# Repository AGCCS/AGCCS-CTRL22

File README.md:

AGCCS-CTRL22
============

We propose a design for a network of EV charging stations compliant to the CCS standard. The repository is organised as follows:

- [./circuit](./circuit/): hardware platform, incl. schematics and a HowTo on firmware installation
- [./ctrl22c](./ctrl22c/): AVR firmware to control the charging process
- [./demesh](./demesh/): ESP32 firmware to organise messaging over a wireless mesh network
- [./monitor](./monitor/): server software for overall control and monitoring of the charging station network
- [./utils](./utils/): scripts to facilitate first-installation and debugging
- [./arduino](./arduino/): Arduino IDE compatible firmware for stand-alone operation (side track)
- [./doc](./doc/): Thesis and other documents regarding this project

**DISCLAIMER 1.** We do not provide a turn-key solution and do not plan to do so in near future. Rather we invite the enthusiast to actively contribute or to passively make use of our collection of resources and to share their experience. We started this project in 2019 and are making steady progress. However, there is still a relevant todo-list. 

**DISCLAIMER 2.** All material provided in this repository comes *'as is'* with no explicit or implied warranty. In particular, the installation of equipment that directly connects to mains power should only by considered by individuals with adequate skills and with particular care.

## Motivation

The Combined Charging System (CCS) provides a specification for low-cost home-charging of electric vehicles (EVs) with up to 22kW. It is based on a simplistic protocol by which the vehicle and the charging station negotiate available power. Of-the-shelf wall-boxes forward the common 3x230V supply at an adjustable current limit to the vehicle via the CCS standard.

The aim of this project is to scale the simplicity of the low-cost single-user wallbox approach to larger parking lots in order to address appartment buildings or shopping venues. These configurations are characterised by a limited and possibly varying amount of available power. Hence, a fixed allocation per parking slot would be inefficient. Instead, we seek for an environment by which individual charging spots communicate and negotiate the power distribution dynamically. Conveivable schemes include first-comes-first-serve, fairness-based-energy-distribution, or ready-to-go-by-schedule. Optionally, an external agent may limit the ussage of non-renewable enery in favour of e.g. available solar power at the given time to the day. 

Our implementation consists of three main components

- a **hardware platform** to implement a relevant subset of the CCS standard
-  **node firmware** to control the charging process and to establish a communication network
- a centralised host for dynamic power allocation and **monitoring** 

All three components are open source and can be hence adapted to best fit a variety of application scenarios.

*From the time we started this project, the market changed a lot and, as of 2021, a number wallboxes with similar features are readily available. However, we believe the an open source approach is still valuable.*

## Hardware Platform

[Our hardware platform](./circuit/) consists of 

+ relevant analog circuitry to implement the specified electronic characteristics
+ an AVR series uC to control the charging process, and
+ an ESP32 SoC to provide means of wireless communication. 

Regarding the analog circuitry, our implementation is derived from the [SmatEVSE project](https://github.com/SmartEVSE). Regarding the uC, we opted for an AVR ATmega to allow for conveniently programming within the Arduino IDE in a long term perspective --- although at this stage the firmware we provide comes 'bare bone' for performance reasons. Regarding the ESP32 SoC, we are fascinated by the powerful SDKs available from Espressif. For our hardware platform, we provide schematics and a PCB Layout, both in editable KiCad format. More detailed documentation is provided in [./circuit/README.md](./circuit/). 

## Node Firmware

Each charging spot comes with an AVR uC for time/safety critical low-level behaviour which communicates via RS232 with an ESP32 for inter-node networking. While the AVR is programed from scratch, the ESP32 firmware builds on the MDF-SDK for wireless mesh-networking. From the latter, we expect a comparatively large area of coverage without additional infrastructure such as Wifi repeaters. Our mesh network subscribes to and publishes from an MQTT broker and is thus interoperable with a wide range of available home automation software. Both, the AVR firmware and the ESP firmware support OTA updates, i.e., no crawling along the parking lot to plug in programming adaptors. More detailed documentation is given by in [./ctrl22c/README.md](./ctrl22c/) for the AVR firmware and by  [./demesh/README.md](./demesh/) for the ESP32 firmware.

## Monitoring Server

At the time of writing, we only provide an elementary monitoring server implemented in Python
for development/testing purposes; see [./utils/README.md](./utils/). This will be substantially updated in the
very near future --- stay tuned.

## Prototype

The below photo shows our hardware (rev 1.2) assembled in an enclosure to include mains contactors, residual current detector/protection and current transformers. It is supplied by three-phases at 32A via the CEE plug on the left, with power forwarded to the CCS 2 outlet on the right; see [Installation](./Installation.md) for details on the external components and the wiring. 

Test run on an individual vehicle (type Opel Corsa) varying from 3kW to 11kW ... lets control the power ;-)

## How/Where/Why to Get Started

Well, no turn-key solution ... but perhaps some interesting venues for the enthusiast:

- If you are interested in hardware and want to assemble your very own CCS implementation there are only a view likewise open projects, e.g., [SmartEVSE](https://www.smartevse.nl/) and [OpenEVSE](https://www.openevse.com/). You are invited to inspect our proposed [./circuit](./circuit/), compare the specifications and take your choice.
- If you are interested in ESP32 mesh networking, perhaps for a completely different target application, feel free to run our implementation [./demesh](./demesh/) in stand-alone mode on common ESP32 dev-boards or more conveniently on M5Sticks. Features include OTA firmware update, control via MQTT and/or plain TCP sockets, synchronised system time, Optiboot (STK500) programming of a target AVR uC.

## Contributors

This project is an initiative by Christoph Pflaum and Thomas Moor, both with FAU/Erlangen/Germany. We appreciate the following contributions by our students/staff.

- Roland Kießling: electrics/electronics lab support, including design and assembly of the prototype enclosures. 

- Pascal Thurnherr: [BA thesis](./doc/Bachelorarbeit_Pascal_Thurnherr.pdf) , _Aufbau und Test einer Ladeneinrichtung für Elektrofahrzeuge nach IEC62169_, FAU/Erlangen 2020; see also [this project](https://github.com/dreadnomad/FGCCS-Ctrl22).

- Antoine Schultz: BA thesis *Firmwareverwaltung drahtlos vernetzter Kleinstrechner mit angekoppelten Mikroprozessoren*, FAU/Erlangen 2020.

- Xinhuang Gong: [MA thesis](./doc/Masterthesis_Xinhuang_Gong.pdf), *Software Infrastructure for a Distributed EV Charging System*, FAU/Erlangen 2021.

- Mark Brieger: MA thesis, *IT Security in home automation — Analysis of connected EV charging stations*, FAU/Erlangen 2021. The study includes a detailed security analysis of the AGCCS hard- and software, and, doing so, reveals a number of relevant vulnerabilities. The majority of these issues has been fixed by Mark, the remainder will be addressed in due course.   

## Acknowledgements

The Wikipedia articles on the [SAE 1772](https://de.wikipedia.org/wiki/SAE_J1772nd), the [IEC 62196](https://de.wikipedia.org/wiki/IEC_62196)  and the [IEC 62196 Type 2](https://de.wikipedia.org/wiki/IEC_62196_Typ_2) standards provide an excellent entry point to learn about EV charging technology and we would like to thank the respective authors for their effort. Regarding the electrical engineeering aspects of this project, we hereby acknowledge the projects [SmartEVSE](https://www.smartevse.nl/) and [OpenEVSE](https://www.openevse.com/), which make their circuitry available for us to inspect and re-use. Starting from scratch would have been so much more tedious. On a more general scale, we appreciate the fact that nowerdays relevent software tools are made freely available, such as the [KiCad EDA](https://kicad.org) , the [Espressif SDKs](https://github.com/espressif), and the [GCC](https://gcc.gnu.org/)-based XTENSA and AVR toolchains, naming only the ones most crucial for our project.

## Copyright/License

All software compents in this project are _"Copyright by the Authors"_ and have been developed independently and from scratch. We provide them as _"Open Source"_ under terms of the MIT License, the Apache License, and/or the GPL, as indicated in the respective code headers. In particular, you are invited to re-cycle whatever you find useful in whatever project you are after. In the case you feel that you gained a relevant benefit from our work, we would appreciate an acknowledgement, e.g., by linking to our GitHub repository. Regarding the hardware circuitry, our work in relevant aspects is a derivative of [SmartEVSE](https://www.smartevse.nl/) distributed as _"Open Source"_ via [GitHub](https://github.com/SmartEVSE) with no specific license stated, and we pass on our contributions to the circuitry likewise.

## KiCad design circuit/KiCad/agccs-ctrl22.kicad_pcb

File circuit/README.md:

Circuitry
=======

The [schematics](agccs-ctrl22-schematics.pdf ) proposed here have been derived from the [SmatEVSE project](https://github.com/SmartEVSE) with a number of modifications in order to

- have an AVR uC from the ATmega series to attract developers from the Arduino community;
- have an ESP32 for networked wireless communications;
- enable/disable any of the three supply phases separately for improved load balancing;
- integrate power monitoring for improved load balancing;
- have a signal relay to virtually unplug/plug the EV to wake it from "sleep"; 
- layout with hand soldering in mind so we can build our own.

When we started AGCCS, we thought of modding SmartEVSE units to our specific needs. However, it soon became clear that this is not vialable, so we decided to design our own board.  

The original adaption to address our requirements was developed in course of the BA thesis *Entwicklung, Aufbau und Test einer Ladeeinrichtung für Elektrofahrzeuge nach IEC62169* by Pascal Thurnherr at FAU/Erlangen and has been published in [this project](https://github.com/dreadnomad/FGCCS-Ctrl22). This folder of the present repository is a strip down to the essentials. You may want to inspect the original sources; in particular the [BA thesis](../doc/Bachelorarbeit_Pascal_Thurnherr.pdf) includes a convenient summary of the electrical specifications from the CCS standard IEC-62196, as far as relevant for the project at hand.

# Theory of Operation in a Nutshell

We use an ATmega 4808 AVR uC to control the charging process. Its core tasks are to

- operate the mains relays to turn on/off individual phases of the charging outlet;
- generate the control pilot signal (CP) to indicate to the EV the amount of power available;
- read back the buffered CP signal to figure the status of the EV (e.g. present, charging);
- read the proximity pilot (PP) to figure the current limit implied by the charging cable;
- read back the current actually drawn.    

For details on the external components and the overall wiring, see  see [../Installation.md](../Installation.md).  

The AVR, runs the firmware [../ctrl22c](../ctrl22c/) which is configured via a human readable protocol on the serial port TX0/RX0, accessible also via J4 for development and testing. **Note that our circuit is 3.3V and you will hence need a 3.3V USB-to-serial converter or a suitable level shifter to access J4.** Once configured, the AVR safely controls the charging process in a stand-alone fashion. The optional ESP32 is utilised to set up a wireless mesh network such that a remote server can re-configure the AVR, e.g. set power limits, enable/disable individual mains phases.  The programming header J5 is used to bootstrap firmware installation (details given below). Once set, further firmware updates can be organised by the remote host, e.g., by the utility `dmctrl.py`; see [../utils](../utils/). 

# Functional Units

Our circuit consists of a number of largely independent functional units that each implement a specific aspect of the charging process. Have the [schematics](agccs-ctrl22-schematics.pdf ) at hand for the following walk through.

**Control Pilot (CP).** The CP signal implements a bidirectional communication with the EV. The charging station outputs a rectangular PWM signal at 1kHz with an amplitude of +/- 12V. This includes the special case of a 100% duty cycle, where we output constantly at +12V. The output stage of the PWM signal is implemented by the general purpose OpAmp LM7332, labeled U11B. It is wired as a comparator and thus converts the 0V/3.3V PWM signal generated by the AVR to the required +/-12V level. By the series resistor R23, the output impedance is effectively set to 1k. If the EV draws a load on the CP signal, the level will drop according  to the load impedance. The second half of the LM7332, labeled U11A, reads back the level of the CP signal and buffers it for reading via an ADC of the AVR. E.g., if the EV imposes a load of 1k during the active duty cycle, the +12V will reduce to +6V. The relevant standard specifies the levels +12V (no car present), +9V (car presents), +6V (car ready to charge or charging) and +3V (ventilation required), each with a certain tolerance. The charging station begins by outputting constant +12V and waits for a drop down to 9V by the EV, i.e., detecting its arrival. The charging station then applies a certain duty-cycle by which the the EV is informed how much current it may draw. Here, the range  of 10% up to 85% linearly corresponds to the range 6A to 80A. It is by specification only that the EV does not use more power, i.e., there is no active current control/limitation in the charging station, mains is forwarded by simple contactors directly to the EV. If the vehicles accepts the offered amount of power, it further lowers CP down to 6V and begins charging. Once charging is completed, the EV releases CP to raise to 9V or above.

**Proximity Pilot (PP).** Charging cables come with a limited capacity, which is encoded by a resistor in the plug to pull the PP line to ground. Our circuit applies a known reference voltage at a known impedance to the PP line and forwards the voltage drop to an ADC of the AVR. Thus, the AVR can decode the voltage reading to conclude the cable capacity.

**Current Monitoring.** Our circuit reads back from external current transformers (CT1, CT2, CT3) in order to measure the AC current actually drawn on each individual phases L1, L2 and L3. We envisage that this will provide us interesting options in the later development of different load-balancing schemes. The current transformers are mounted such that each individual phase runs through the respective transformer. The induced voltage is then approximately linear to the current drawn. This voltage is forwarded to the AVR for regular sampling such that the RMS value can be calculated. Although this construct can not be expected to measure the current overly precise, we can detect when the current starts to drop and hence adjust the PWM signal on CP accordingly. Thus, the overall available power can be re-allocated to other charging stations. If you consider current motinoring for billing puposes, you should use an external calibrated meter. If so, get one with RS485 so you can attach it to our circuit and eliminate the need for the current transformers.

**Cable Lock.** The charging cable must not be unplugged while charging. For this reason, charging outlets have a mechanical lock to hold on the cable. We heard of different styles of locks, however, the principle of operation appears to be all the same. The lock has two main connectors. Depending on the polarity, the lock is engaged or released. Our circuit utilises the general purpose two channel MOSFET driver FAN3214TMX  U5 to implement this feature. With input A logic high and input B logic low it actively drives the external line Lock_R to 12V and the external line Lock_W to GND. Likewise, A logic low and  B logic high does the converse. How to wire the lock correctly is easily figured by experiment. In order for the AVR to sense the lock state, the lock is also equipped with a contact, which typically is closed when the lock is closed. To save on wiring, we set A and B both to logic high when not operating the lock, so we can route 12V via the contact back to the AVR in order to sense line Lock_B. The typical overall setup is as follows:

```
Lock_W >---------------------[ actuator ] ---+
                                             |
Lock_R >-------------------------------------+
                                             |
Lock_B <---------------------[ contact ]-----+
```

Here it is assumed that the lock closes when Lock_R is driven to 12V while Lock_W is driven to GND. Note: although functional, we are not quite happy with our choice of the FAN3214TMX for the given purpose and we are prepared to address this in a subsequent revision.

**Power Rails**. Our circuit generates the relevant power rails +12V, -12V and +3.3V in the usual manner using two cascaded switching regulators and a voltage inverter. The +12V rail is obtained by an integrated component directly from mains. We have opted for 800mA as a reasonable maximum rating. However, the lock motor (or solenoid) will draw up to 3A on operation. Thus, we buffer the 12V line via the Schottky diode D12 and the capacitor C12 [rated 15000uF]  with the current limiting resistor R3-R6 [typ. 25R]. The resistor limits the maximum current on the 12V rail to about 500mA while the low voltage across D12 assures a charge up to almost 12V. Since the closing or the opening of the lock only takes a view ms [we experienced approx. 20ms], the mechanism is effectively driven by the energy held up in the capacitor C12. As a side effect, this construct allows us to address brown-out situations: at power loss during charging we shall release the lock. Since power loss may be caused by issues with the charging process in conjunction with mandatory residual current detection, this scenario is more likely than it appears and being locked on power failure would make our clients really unhappy. We therefor generate the brown-out signal  BOT when the 12V rail falls below approx. 10V, leaving the AVR time to release the lock via the remaining charge of capacitor C12. The minimum dimension of C12 will crucially depend on the actual lock.  **Not all locks are the same:** if you plan to use a lock, you should check on the values of C12 and R3-R6. Charge C12, disconnect power and test whether you can open/close the lock. If you plan on additional units living on the 12V rail, you may want to increase R3-R6 in order to reduce the current drawn while charging C12.

**Digital IOs.** Our circuitry includes digital IOs for an operator button, an operator indicator (LED)  and to individually control each of the three phases L1, L2 and L3 via external contactors, driven by the SSRs  U1, U2 and U3. In addition, we have included the signal relays U12 and U13 to virtually disconnect the EV from the charging station. Since certain EVs will "fall to sleep" when charging does non commence within a certain amount of time, the signal relay becomes relevant when charging by schedule or power allocation by an external agent; e.g. only start charging when solar power is available. 

# Installing Firmware (first time only)

To get bootstrapped, we need to install an initial version of firmware for both the AVR uC and the ESP32 SoC. For this purpose, our board is equipped with the custom 8-pin header J5. For your own convenience, we propose that you set up a programming adaptor following these  [schematics](agccs-j5adaptor-schematic.pdf ). 

|  Fnct.   | Pin  | Pin  |  Fnct.   |
| :------: | :--: | :--: | :------: |
| AVR-UPDI |  1   |  2   |   GND    |
| ESP-TX0  |  3   |  4   |   3.3V   |
| ESP-RX0  |  5   |  6   | ESP-IO15 |
| ESP-IO0  |  7   |  8   |  ESP-EN  |

### AVR Firmware/Bootloader

The ATmega4808 used in our project is a modern incarnation of the ATmega series, and in many aspects more closely related to the Xmega series than to clasical ATmegas. You will need a fairly recent version of `avr-gcc`, `avr-libc` and `avr-binutils` (verified with versions 7.3, 2.0.0 and 2.26, respectively):

- for Linux an appropriate toolchain should be supplied by your distribution (verified for Debian; should be the same for many popular Debian derivates);
- for Mac OSX and Windows, the most pragmatic way to get a recent toolchain is to borrow it from an up-to-date Arduino installation (look for `_where_ever_Ardiono_is/Java/hardware/tools/avr/bin/` and set your `PATH` environment variable accordingly). 

Another speciality of the XMega series inherited by the ATmega4808 is that they are natively programmed via the so called UPDI one-pin interface. The official programmer *Atmel ICE* ($100+) works fine with Windows and Atmel AVR Studio (Version 7 or later) and provides professional grade debugging facilities. However, at the time of writing, *Atmel ICE* is not so well supported by mainstream `avrdude` and may not be accessible via Linux/Mac OSX. Fortunately, the [`pyudpi project`](https://github.com/mraardvark/pyupdi) provides a low-cost alternative which only needs an of the shelf USB-to-serial converter and a single 4.7K resistor --- we used this approach with no problems at all on Mac OSX and Linux. **Again: you will need a 3.3V USB-serial converter - do not trust the labels, use your scope/meter - otherwise you risk to fry your AVR**.

Short instructions:

- set up the wiring
  ```
  USB-Serial-TX>---[4.7K]--->+---<>AVR-UPDI (aka connector J5 pin 1)
                             |
  USB-Serial-RX>-------------+
  USB-Serisl-GND<>---------------<>GND  (aka connector J5 pin 2)
  ```
  
- get  [`pyudpi`](https://github.com/mraardvark/pyupdi)from Github; the 2021-02 version installs via `pip` and requires python3

- get some AVR device specs and check the connection

  ```
  pyupdi.py -d mega4808 -c /dev/{SOME_USB_SERIAL_DEV} -b 115200 -i
  ```

- read fuses 

  ```
  pyupdi.py -d mega4808 -c /dev/{SOME_USB_SERIAL_DEV} -b 115200 -fr
  ```

- write fuses

  ```
  pyupdi.py -d mega4808 -c /dev/{SOME_USB_SERIAL_DEV} -b 115200 -fs {ADDRESS}:{VALUE}
  ```

   {ADDRESS}:{VALUE} is specified in the output format of `-fr`, e.g.,  `8:0x02` to set BOOTEND to 0x02 as propsoed below.

- program flash memory, e.g. the Optiboot bootloader

  ```
  pyupdi.py -d mega4808 -c /dev/{SOME_USB_SERIAL_DEV} -b 115200 -f {OPTIBOOT_FOR_ATM4808}.hex
  ```

Although you can flash any firmware via the routine described above, we need a bootloader for our project such that later firmware updates can be organised remotely. We use Optiboot for its compliance with the Arduino toolchain. Get your original copy of [Optiboot](https://github.com/Optiboot) or use the `.hex` file provided in our repository. 

**Note:** in flash, Optiboot is located in the range from 0x0000 to 0x1ff and thus takes 512bytes. Hence if you use Optiboot, the `BOOTEND` fuse of the ATmega4808 needs to be set to 0x02. The overall setting of fuses depends of the actual firmware. For the provided firmware [Ctrl22C](../ctrl22c/) we use the following settings

| address:value | fuse     | comments                                                     |
| ------------- | -------- | ------------------------------------------------------------ |
| 0:0x00        | WDTCFG   | default 0x00, no watchdog                                    |
| 1:0x00        | BODCFG   | default 0x00, test for1.8V@1kHz, disabled (see BOD.CTRLA)    |
| 2:0x02        | OSCLOCK  | default 0x02, use 20MHz oscillator (which we later divide by 2) |
| **5:0xC9**    | SYSCFG0  | default 0xE4, no application CRC, **have RESET pin**, **keep EEPROM on flash erase** |
| 6:0x06        | SYSCFG1  | default 0x07, 64ms start-up-time on power on                 |
| 7:0x00        | APPEND   | defaut 0x00, no explicit data section                        |
| **8:0x02**    | BOOTEND  | default 0x00, **have 2x256bytes bootloader**                 |
| 10:0xC5       | LOCKBITS | default 0xC5, no locks, i.e., UPDI fully enabled             |

### ESP32 Firmware

The ESP32 SoC is far more advanced than a plain AVR uC. It has a factory-built-in two-level boot loader and is programmed via the serial interface TX0/RX0. To enter application boot loader mode, IO0 must be set low at the time when EN becomes high (EN acts as inverted RESET, and IO0 selects the boot mode).

Short instructions:
- set up the ESP32-MDF SDK and compile the firmware `demesh`; see [../demesh](../demesh/) for a concise introductions; 
- set up the wiring
  ```
  USB-Serial-TX>------------->ESP-RX0  (aka connector J5 pin 5)
  USB-Serial-RX<-------------<ESP-TX0  (aka connector J5 pin 3)
  USB-Serisl-GND<>---+------<>GND      (aka connector J5 pin 2)
                     |
                     +-[/]--<>ESP-IO0  (aka connector J5 pin 7)
                     |
                     +-[/]--->ESP-EN   (aka connector J5 pin 8)
  ```
- to flash the `demesh` firmware
  - set ESP-EN and ESP-IO0 to low (on our adaptor: press the black and the grey button)
  - set ESP-EN to not-connected (on our adaptor: release the black button)
  - run `make flash`
  - set ESP-IO0 to not-connected (on our adaptor: release all buttons)

This is effectively the same procedure as with common ESP32 dev-boards such as NodeMCU, except that the dev-boards will have convenient key-switches and USB-to-Serial converters built-in while we need to do some external wiring. **One last word of warning: make sure your USB-to-Serial converter is 3.3V.**

# Developing/Testing AVR Firmware

Assuming that you have installed Optiboot as described above, application firmware can be installed and tested via the J4 header in *Arduino* style, i.e., serial debugging via a terminal emulation and firmware flashing over the same serial line using `avrdude -carduino`. If you go this path, we recommend you set up a simple adaptor including a key-switch on the AVR reset-line to conveniently enter bootloader mode, e.g.

```
USB-Serial-RX<-------------<AVR-TX0  (aka connector J4 pin 2)
USB-Serial-TX<-------------<AVR-RX0  (aka connector J4 pin 3)
USB-Serisl-GND<>---+------<>GND      (aka connector J4 pin 1)
                   |
                   +-[/]--<>AVR-RST  (aka connector J4 pin 4)

```

**Advanced Topic:** feel free to get an USB-to-Serial converter with DTR and wire DTR via an high-pass strategically to AVR-RST; e.g., copy the original Arduino schematics in this regard.  Your AGCCS board is then conveniently one-click programmable from the Arduino IDE (using the [MegaCoreX](https://github.com/MCUdude/MegaCoreX) extension to support the ATmega4808).

However, if you have installed the ESP32 with the provided firmware `demesh`, there is an even more convenient and --- given that we are running on mains power --- more safe alternative. On power-on, `demesh` reads IO15. When pulled down to GND it chooses to boot into *target-development mode*. In this mode it will not setup a wifi mesh network but instead act as an access point and provide a transparent telnet passthrough of the AVR serial port TX0/RX0 incl. the Optiboot boot loader. Thus, we can develop/test the AVR firmware largely independently from the more involved wifi mesh but still have the convenience of "no wires from inside the charging station directly to the computer".

After connecting with the access point, the debug server can be accessed via telnet on the standard port 23; e.g.

```
gtelnet 192.168.4.1
```

The IP address, the SSID (default `DebugAVR`) and the WPA2 password are configured within `demesh`; see [../demesh](../demesh/). To inspect available commands for the provided AVR firmware, type `? [CR]`. To exit the session, type `Ctrl-Q` or `Ctrl-D`.

To access the AVR bootloader, the alternative port 2323 is provided. On connection, it resets the AVR to enter Optiboot an can thus be programmed via `avrdude -carduino`. Example 

```
avrdude -patmega4808  -carduino -Pnet:192.168.4.1:2323 -U flash:w:{SOME_HEX_FILE}.hex
```

**Note:** In contrast to the classic ATmega architecture, the ATmega4808 has the boot loader in low address range and, hence, the load address of the application firmware needs to be adjusted accordingly. Optiboot is located in the range 0x0000 to 0x01ff and expects the application to load at 0x0200. This needs to be made explicit when compiling the application firmware, e.g., with the linker directive `--section-start=.text=0x200`. The `makefile` provided with our firmware [Ctrl22C](../ctrl22c/) will take care about this detail.  

# Hardware Revisions

In this repository we provide the current state of development Rev-1-x and the latest stable version Rev-1-2, both as editable KiCad projects. For documentation purposes, earlier revisions are provided as PDFs for inspection. 

The initial revision Rev-1-0 passed our tests conducted with a first-installation firmware archived in [Pascal Thurnherrs repository](https://github.com/dreadnomad/FGCCS-Ctrl22). Rev-1-1 is an incremental upgrade by the same team, it should be fine too from an electronics perspective. As of June 2021, we have assembled three prototypes of our intermediate finalist Rev-1-2. All functional units passed basic tests, e.g., we can drive the contactors and generate/read-back the CP signal using the current version of the production firmware [Ctrl22C](../ctrl22c/).  We used this setup to charge an Opel Corsa with no issues whatsoever. Tests included dynamic control of allocated power to a max of 11kW (as limited by our local supply), as well as pause/resume.

## Revision 1.0

- initial release by Pascal Thurnherr
- thoroughly tested on a component level; e.g, accurate generation of CP and reading the imposed load
- a number of minor hickups, however, with a slightly modded version we actually managed to charge Christophs EV with Pascals first-installation firmware 

## Revision 1.1

- seperate terminals J1/J2 and J6/J7 to fit common housings
- additional protection BAT54S for analog inputs CT1-CT3
- improved pinout of J5 and J4 (programming headers)
- improved pinout on J6/J7 and J1/J2 (simplify external wiring)
- reduced lock resistor from 50 to 25 as learned from Rev-1-0 and our particular lock
- clear indication of C16 polarity
- reduced current on button-press

- fixed footprint of power supply
- placed ESP32 on backside for the option of an external antenna

## Revision 1.2

- jet again the push button electronics ... this time we should have got them right

- brown out detection incl. "opening lock on power down"

- improved current reading circuitry to decouple individual phases

- further optimized the spacing in the layour for hand soldering

- general tidying up schematics and the layout 

## Revision 1.x

- minor flaws in 1.2 PCB layout  (weak fill on backside layer, not so nice front silk screen)
- although functional in practice, we are not quite happy with the lock driving circuitry and plan on improvements on that end  

## Photos (Rev.1.2)

Front (in terms of PCB design; in the enclosure, this actually becomes the backside)

Back (in terms of PCB design; in the enclosure, this becomes the front; note that the 230V/12V converter has not yet been installed, so we can safely power with a bench supply via J3 for testing )

**Some notes on assembly.** SMDs in 0805 format can be soldered by hand using a fine tipp and thin solder; same holds for most of the semiconductors except perhaps the AVR --- solder paste and hot air may be the preference here; since PP is only connected to a resistor within the CCS plug of the charging cable, we almost certainly may short the relay U12 (and hence not populate it); we never actually used the RS485 option (and hence may not even populate U7); watch out, there are smart and less smart orders in which to solder the individual parts depending on their physical dimensions and locations; most parts are to be soldered to the front side, but some go on the back side --- double check; that tantalum capacitor C16 is polarised (!); regarding functional modules, plan for incremental tests, e.g., first install the 3.3V regulator and run/test from a 12V bench supply, then install the AVR minimalistically and program via UPDI (an indicator LED is useful here, may blink TX2 on the extension connector J3), then add the ESP32 and set it to target-AVR debug mode; from now on "no wires from the board to your computer", you can further populate/test individual functional modules safely isolated ... a.s.o. ... the 230V/12V converter comes definitely last; clean your glasses, sharpen your tweezers, have fun.  See also our firmware [Ctrl22C](../ctrl22c/) for recommendations on first installation.

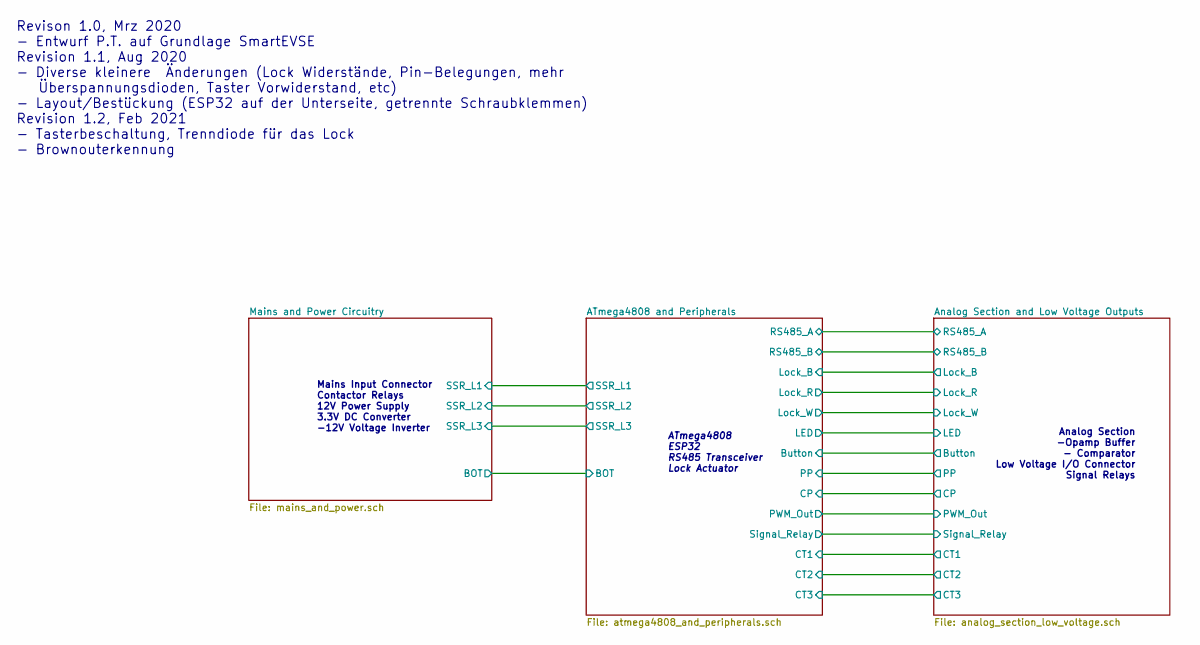
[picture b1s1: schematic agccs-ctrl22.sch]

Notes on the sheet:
Mains Input Connector Contactor Relays 12V Power Supply 3.3V DC Converter -12V Voltage Inverter
ATmega4808 ESP32 RS485 Transceiver Lock Actuator
Analog Section -Opamp Buffer - Comparator Low Voltage I/O Connector Signal Relays
Revison 1.0, Mrz 2020 - Entwurf P.T. auf Grundlage SmartEVSE Revision 1.1, Aug 2020 - Diverse kleinere Änderungen (Lock Widerstände, Pin-Belegungen, mehr Überspannungsdioden, Taster Vorwiderstand, etc) - Layout/Bestückung (ESP32 auf der Unterseite, getrennte Schraubklemmen) Revision 1.2, Feb 2021 -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

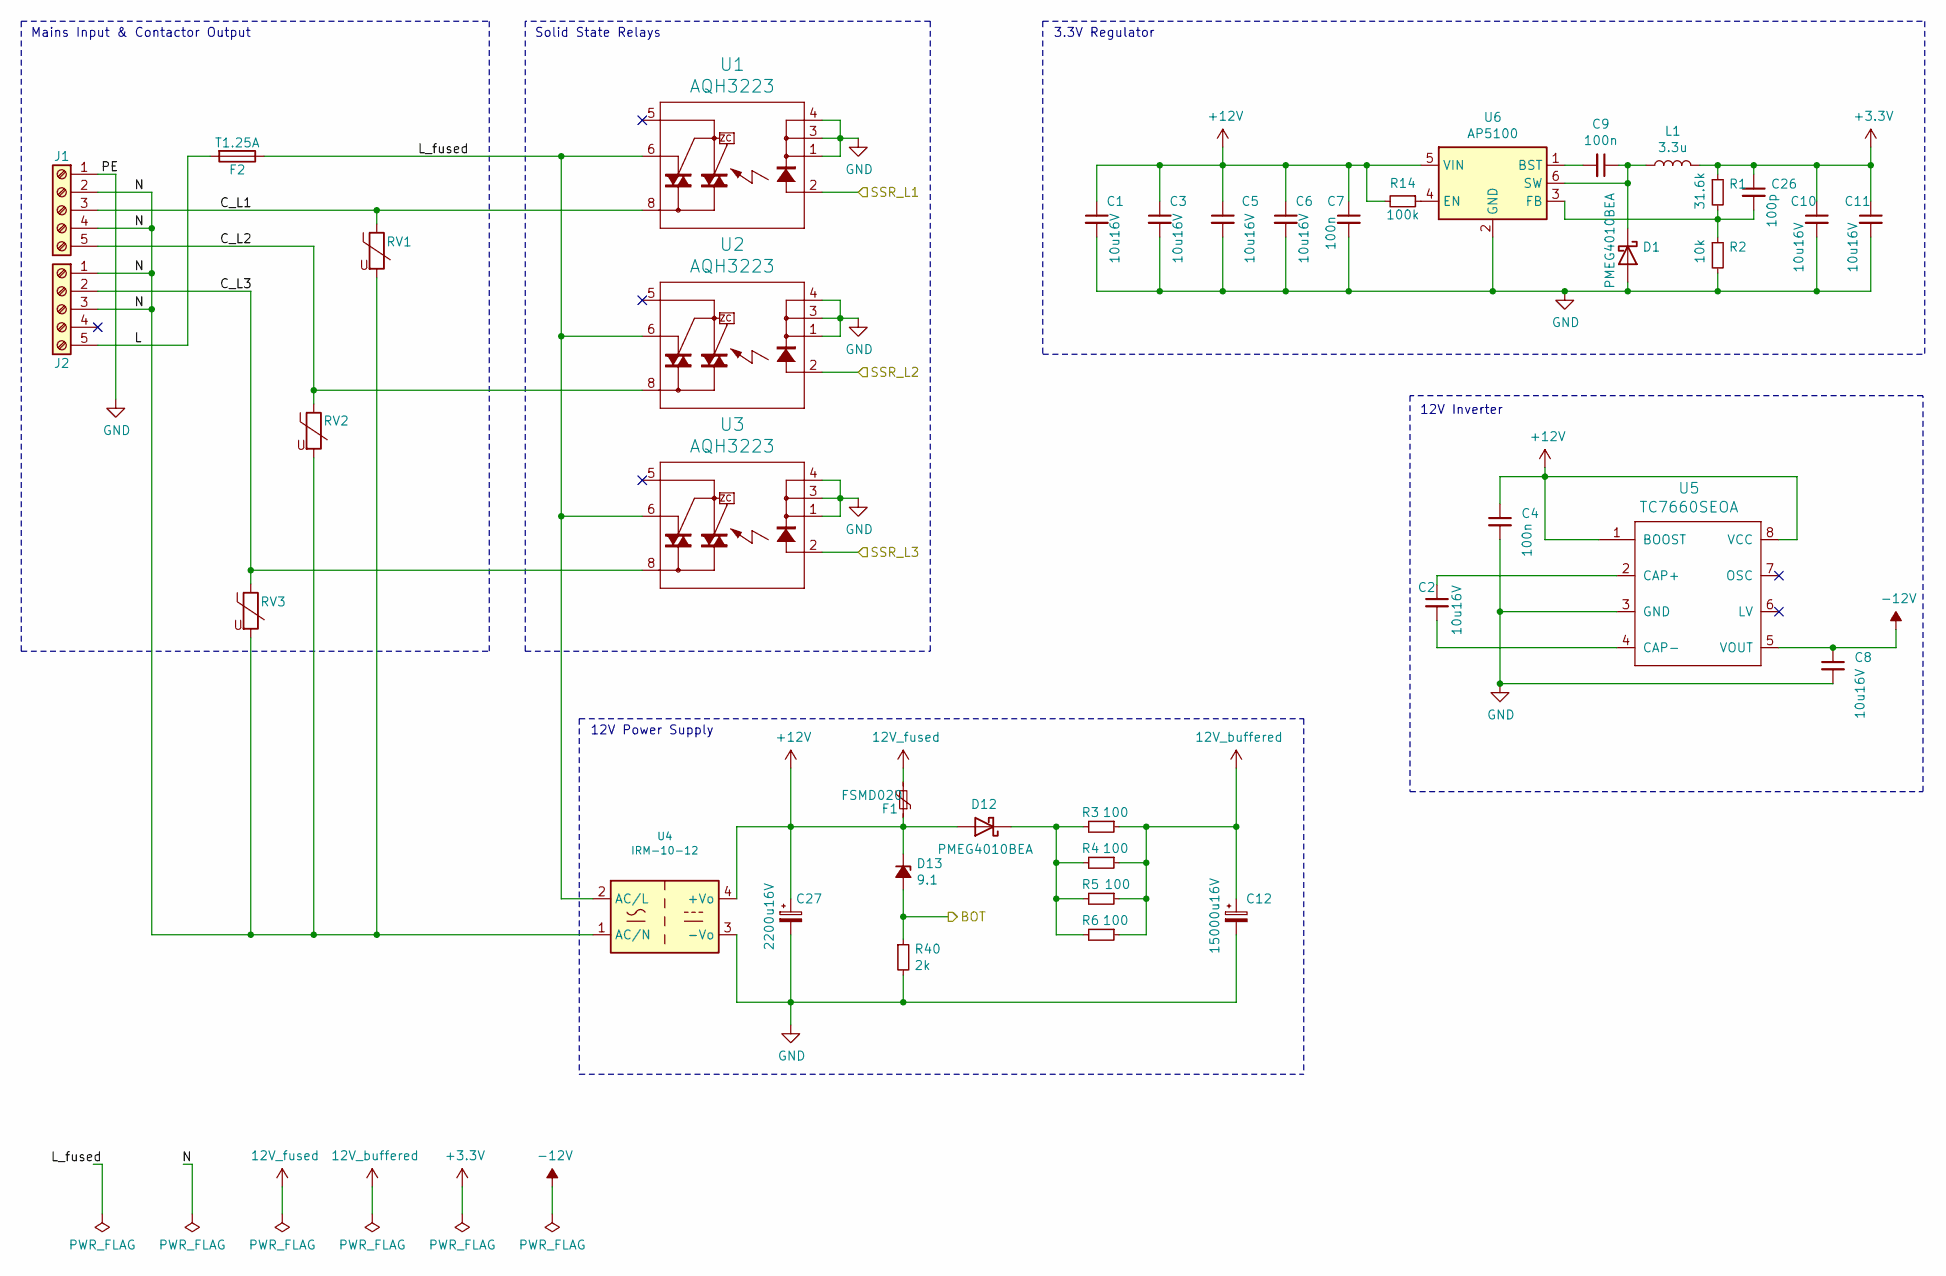
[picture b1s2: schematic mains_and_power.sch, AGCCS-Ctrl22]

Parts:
C1, C2, C3, C5, C6, C8, C10, C11: 10u16V; C_0805_2012Metric_Pad1.18x1.45mm_HandSolder; PartNo 963-EMK212ABJ106MG-T
C4, C7, C9: 100n; C_0805_2012Metric_Pad1.18x1.45mm_HandSolder; PartNo 963-EMF212B7104KGHT
C12: 15000u16V; CP_Radial_D22.0mm_P10.00mm_SnapIn; PartNo 871-B41231A4159M000
C26: 100p; C_0805_2012Metric_Pad1.15x1.40mm_HandSolder; PartNo 77-VJ0805Y101KXACBC
C27: 2200u16V; CP_Radial_D12.5mm_P7.50mm; PartNo 871-B41888C4228M000
D1, D12: PMEG4010BEA; D_SOD-323_HandSoldering; PartNo 771-PMEG4010BEA,135
D13: 9.1; D_SOD-323_HandSoldering; PartNo 621-UDZ9V1BQ-13
F1: FSMD020; Fuse_1812_4532Metric_Pad1.30x3.40mm_HandSolder; PartNo 576-1812L020PR
F2: T1.25A; TE5; PartNo 576-3921125000
J1: Screw_Terminal_01x05; hv_screw_5pin_1; PartNo na
J2: Screw_Terminal_01x05; hv_screw_5pin_2; PartNo 490-TB005-762-10BE
L1: 3.3u; L_1210_3225Metric_Pad1.42x2.65mm_HandSolder; PartNo 810-MLF1608A3R3J
R1: 31.6k; R_0603_1608Metric_Pad1.05x0.95mm_HandSolder; PartNo 594-MCT06030C3162FP5
R2: 10k; R_0603_1608Metric_Pad1.05x0.95mm_HandSolder; PartNo 594-MCT06030C1002FP5
R3, R4, R5, R6: 100; R_0603_1608Metric_Pad1.05x0.95mm_HandSolder; PartNo 490-TB005-762-10BE
R14: 100k; R_0603_1608Metric_Pad1.05x0.95mm_HandSolder; PartNo 594-MCT06030C1003FP5
R40: 2k; R_0603_1608Metric_Pad1.05x0.95mm_HandSolder; PartNo 594-MCT06030C2001FP5
RV1, RV2, RV3: Varistor; RV_Disc_D15.5mm_W5mm_P7.5mm; PartNo 871-B72214S0271K551
U1, U2, U3: AQH3223; DIL07SMD; PartNo 769-AQH1213AX
U4: IRM-10-12; Converter_ACDC_MeanWell_IRM-10-xx_THT; PartNo 709-IRM10-12
U5: TC7660SEOA; SOIC-8_3.9x4.9mm_P1.27mm; PartNo 579-TC7660SEOA
U6: AP5100; SOT-23-6; PartNo 621-AP5100WG-7

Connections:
12V_buffered: C12.1, R3.1, R4.1, R5.1, R6.1; also elsewhere on the board
12V_fused: F1.2; also elsewhere on the board
+3V3: C10.1, C11.1, C26.1, L1.2, R1.1; also elsewhere on the board
+12V: C1.1, C3.1, C4.1, C5.1, C6.1, C7.1, C27.1, D12.2 (A), D13.1 (K), F1.1, R14.2, U4.4 (+Vo), U5.1 (BOOST), U5.8 (VCC), U6.5 (VIN); also elsewhere on the board
-12V: C8.1, U5.5 (VOUT); also elsewhere on the board
/ATmega4808 and Peripherals/BOT: D13.2 (A), R40.1; also elsewhere on the board
/ATmega4808 and Peripherals/SSR_L1: U1.2 (A); also elsewhere on the board
/ATmega4808 and Peripherals/SSR_L2: U2.2 (A); also elsewhere on the board
/ATmega4808 and Peripherals/SSR_L3: U3.2 (A); also elsewhere on the board
/Mains and Power Circuitry/C_L1: J1.3, RV1.1, U1.8 (DS1)
/Mains and Power Circuitry/C_L2: J1.5, RV2.1, U2.8 (DS1)
/Mains and Power Circuitry/C_L3: J2.2, RV3.1, U3.8 (DS1)
/Mains and Power Circuitry/L: F2.2, J2.5
/Mains and Power Circuitry/L_fused: F2.1, U1.6 (DS3), U2.6 (DS3), U3.6 (DS3), U4.2 (AC/L)
/Mains and Power Circuitry/N: J1.2, J1.4, J2.1, J2.3, RV1.2, RV2.2, RV3.2, U4.1 (AC/N)
GND: C1.2, C3.2, C4.2, C5.2, C6.2, C7.2, C8.2, C10.2, C11.2, C12.2, C27.2, D1.2 (A), J1.1, R2.2, R40.2, U1.1 (K), U1.3 (K1), U1.4 (K2), U2.1 (K), U2.3 (K1), U2.4 (K2), U3.1 (K), U3.3 (K1), U3.4 (K2), U4.3 (-Vo), U5.3 (GND), U6.2 (GND); also elsewhere on the board
unnamed: C2.1, U5.2 (CAP+)
unnamed: C2.2, U5.4 (CAP-)
unnamed: C9.1, D1.1 (K), L1.1, U6.6 (SW)
unnamed: C9.2, U6.1 (BST)
unnamed: C26.2, R1.2, R2.1, U6.3 (FB)
unnamed: D12.1 (K), R3.2, R4.2, R5.2, R6.2
unnamed: R14.1, U6.4 (EN)

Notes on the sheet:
Solid State Relays
12V Power Supply
3.3V Regulator
12V Inverter
Mains Input & Contactor Output

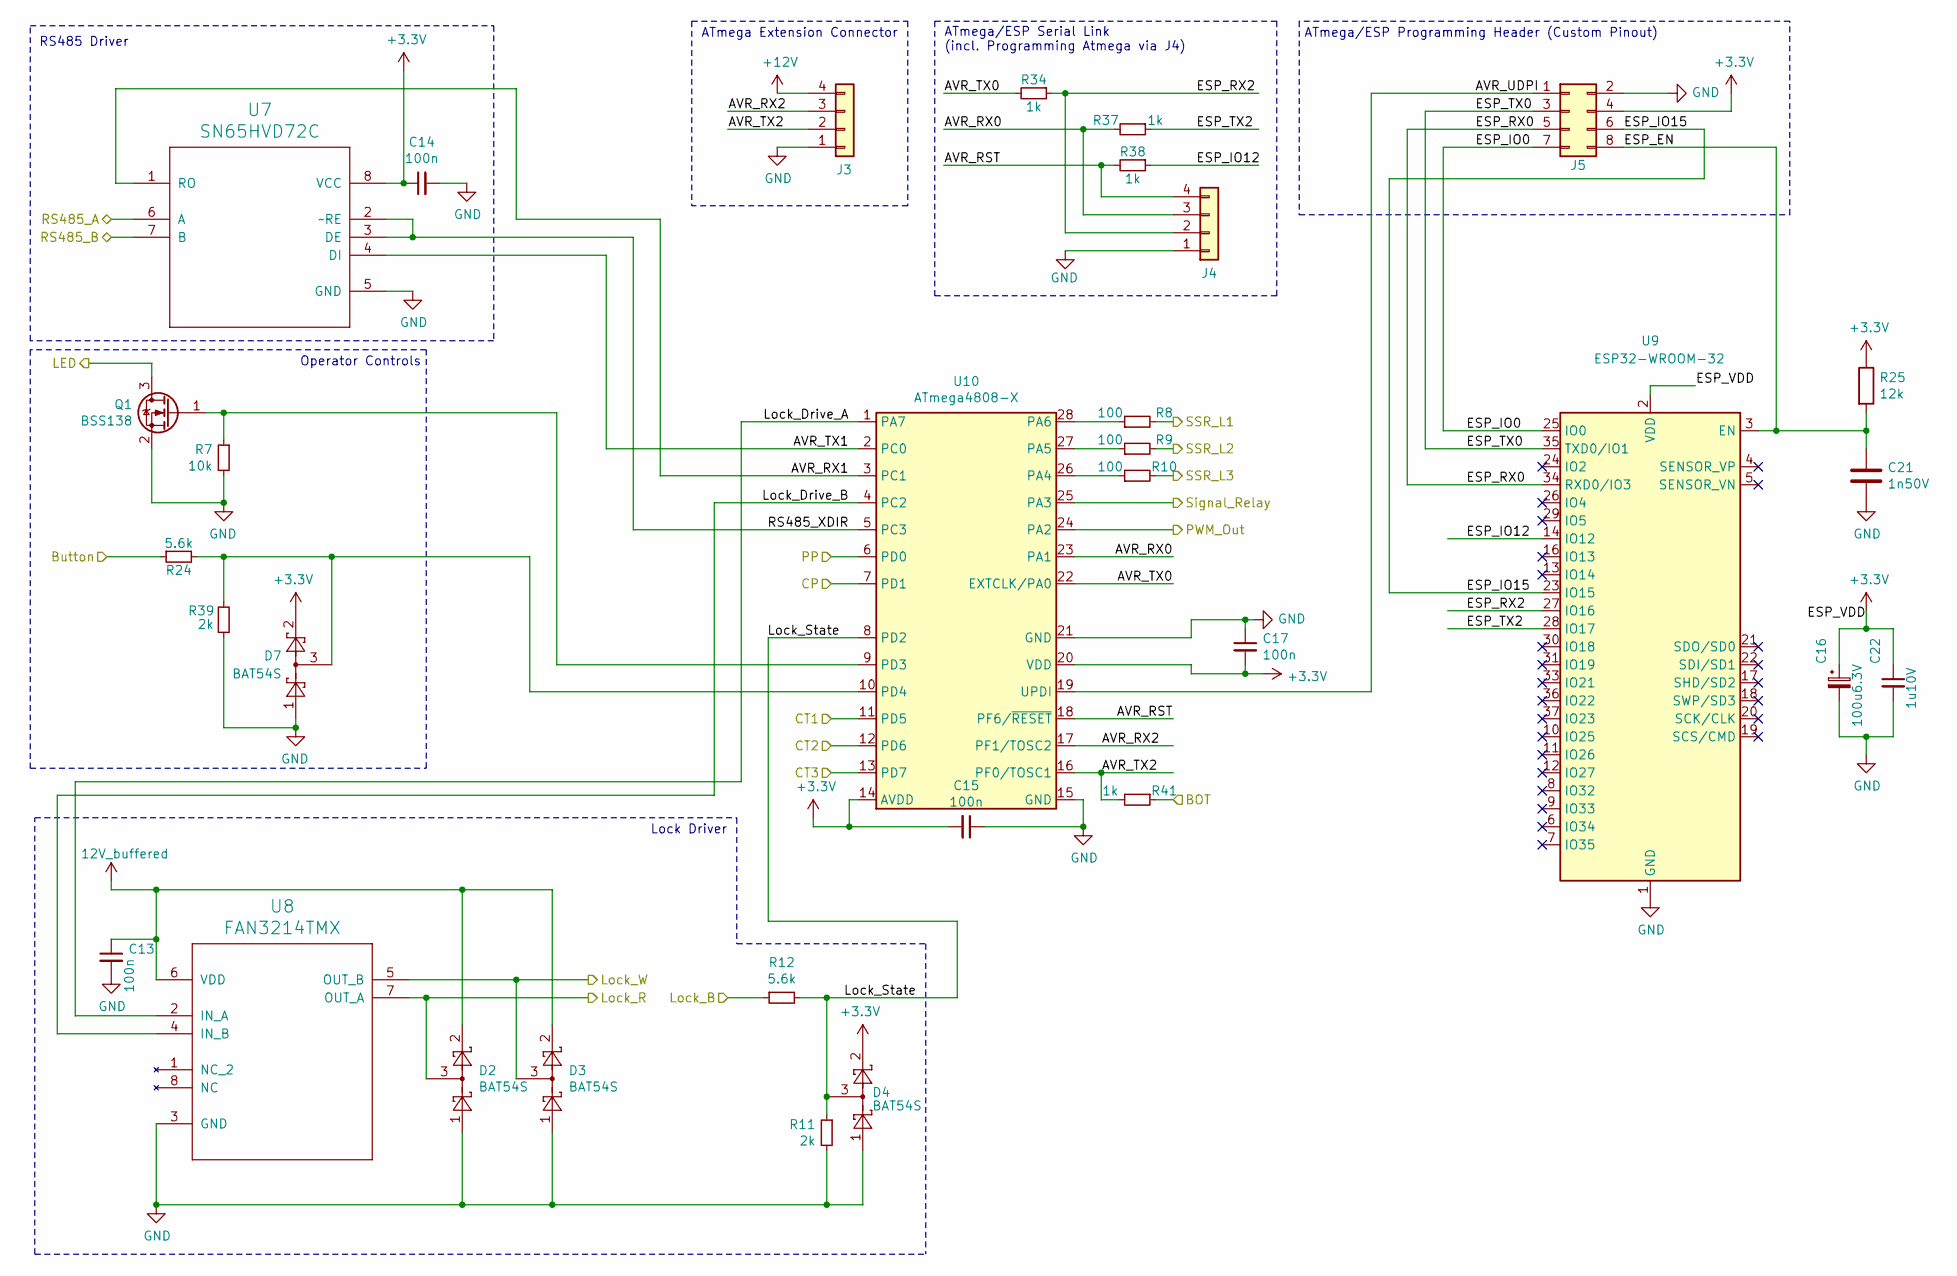
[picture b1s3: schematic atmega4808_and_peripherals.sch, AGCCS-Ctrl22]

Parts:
C13, C14, C15, C17: 100n; C_0805_2012Metric_Pad1.18x1.45mm_HandSolder; PartNo 963-EMF212B7104KGHT
C16: 100u6.3V; CP_EIA-2012-15_AVX-P_Pad1.30x1.05mm_HandSolder; PartNo 581-TLCR107M006RTA
C21: 1n50V; C_0805_2012Metric_Pad1.15x1.40mm_HandSolder; PartNo 77-VJ0805A102KXAAC
C22: 1u10V; C_0805_2012Metric_Pad1.15x1.40mm_HandSolder; PartNo 77-VJ805Y105KXARW1BC
D2, D3, D4, D7: BAT54S; SOT-23_Handsoldering; PartNo 757-TBAT54SLM
J3: Conn_01x04; UART2-Header; PartNo 710-61304011121
J4: Conn_01x04; UART0-Header; PartNo na
J5: Conn_02x04; PROGRAM-Header; PartNo 710-61200821621
Q1: BSS138; SOT-23_Handsoldering; PartNo 512-BSS138
R7: 10k; R_0603_1608Metric_Pad1.05x0.95mm_HandSolder; PartNo 594-MCT06030C1002FP5
R8, R9, R10: 100; R_0603_1608Metric_Pad1.05x0.95mm_HandSolder; PartNo 490-TB005-762-10BE
R11, R39: 2k; R_0603_1608Metric_Pad1.05x0.95mm_HandSolder; PartNo 594-MCT06030C2001FP5
R12, R24: 5.6k; R_0603_1608Metric_Pad1.05x0.95mm_HandSolder; PartNo 594-MCT06030C5601FP5
R25: 12k; R_0603_1608Metric_Pad1.05x0.95mm_HandSolder; PartNo 594-MCT06030C1202FP5
R34, R37, R38, R41: 1k; R_0603_1608Metric_Pad1.05x0.95mm_HandSolder; PartNo 594-MCT06030C1001FP5
U7: SN65HVD72C; SOIC-8_3.9x4.9mm_P1.27mm; PartNo 595-SN65HVD72D
U8: FAN3214TMX; SOIC-8_3.9x4.9mm_P1.27mm; PartNo 512-FAN3214TMX
U9: ESP32-WROOM-32; PartNo 356-ESP32WRM32E128PH
U10: ATmega4808-X; SSOP-28_5.3x10.2mm_P0.65mm; PartNo 556-ATMEGA4808-XF

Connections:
12V_buffered: C13.1, D2.2, D3.2, U8.6 (VDD); also elsewhere on the board
+3V3: C14.1, C15.2, C16.1, C17.2, C22.1, D4.2, D7.2, J5.4, R25.1, U7.8 (VCC), U9.2 (VDD), U10.14 (AVDD), U10.20 (VDD); also elsewhere on the board
+12V: J3.4; also elsewhere on the board
/ATmega4808 and Peripherals/AVR_RST: J4.4, R38.2, U10.18 (PF6/~RESET)
/ATmega4808 and Peripherals/AVR_RX0: J4.3, R37.2, U10.23 (PA1)
/ATmega4808 and Peripherals/AVR_RX1: U7.1 (RO), U10.3 (PC1)
/ATmega4808 and Peripherals/AVR_RX2: J3.3, U10.17 (PF1/TOSC2)
/ATmega4808 and Peripherals/AVR_TX0: R34.2, U10.22 (EXTCLK/PA0)
/ATmega4808 and Peripherals/AVR_TX1: U7.4 (DI), U10.2 (PC0)
/ATmega4808 and Peripherals/AVR_TX2: J3.2, R41.2, U10.16 (PF0/TOSC1)
/ATmega4808 and Peripherals/AVR_UDPI: J5.1, U10.19 (UPDI)
/ATmega4808 and Peripherals/BOT: R41.1; also elsewhere on the board
/ATmega4808 and Peripherals/Button: R24.1; also elsewhere on the board
/ATmega4808 and Peripherals/CP: U10.7 (PD1); also elsewhere on the board
/ATmega4808 and Peripherals/CT1: U10.11 (PD5); also elsewhere on the board
/ATmega4808 and Peripherals/CT2: U10.12 (PD6); also elsewhere on the board
/ATmega4808 and Peripherals/CT3: U10.13 (PD7); also elsewhere on the board
/ATmega4808 and Peripherals/ESP_EN: C21.1, J5.8, R25.2, U9.3 (EN)
/ATmega4808 and Peripherals/ESP_IO0: J5.7, U9.25 (IO0)
/ATmega4808 and Peripherals/ESP_IO12: R38.1, U9.14 (IO12)
/ATmega4808 and Peripherals/ESP_IO15: J5.6, U9.23 (IO15)
/ATmega4808 and Peripherals/ESP_RX0: J5.5, U9.34 (RXD0/IO3)
/ATmega4808 and Peripherals/ESP_RX2: J4.2, R34.1, U9.27 (IO16)
/ATmega4808 and Peripherals/ESP_TX0: J5.3, U9.35 (TXD0/IO1)
/ATmega4808 and Peripherals/ESP_TX2: R37.1, U9.28 (IO17)
/ATmega4808 and Peripherals/LED: Q1.3 (D); also elsewhere on the board
/ATmega4808 and Peripherals/Lock_B: R12.1; also elsewhere on the board
/ATmega4808 and Peripherals/Lock_Drive_A: U8.2 (IN_A), U10.1 (PA7)
/ATmega4808 and Peripherals/Lock_Drive_B: U8.4 (IN_B), U10.4 (PC2)
/ATmega4808 and Peripherals/Lock_R: D2.3, U8.7 (OUT_A); also elsewhere on the board
/ATmega4808 and Peripherals/Lock_State: D4.3, R11.1, R12.2, U10.8 (PD2)
/ATmega4808 and Peripherals/Lock_W: D3.3, U8.5 (OUT_B); also elsewhere on the board
/ATmega4808 and Peripherals/PP: U10.6 (PD0); also elsewhere on the board
/ATmega4808 and Peripherals/PWM_Out: U10.24 (PA2); also elsewhere on the board
/ATmega4808 and Peripherals/RS485_A: U7.6 (A); also elsewhere on the board
/ATmega4808 and Peripherals/RS485_B: U7.7 (B); also elsewhere on the board
/ATmega4808 and Peripherals/RS485_XDIR: U7.2 (~~RE), U7.3 (DE), U10.5 (PC3)
/ATmega4808 and Peripherals/SSR_L1: R8.2; also elsewhere on the board
/ATmega4808 and Peripherals/SSR_L2: R9.2; also elsewhere on the board
/ATmega4808 and Peripherals/SSR_L3: R10.2; also elsewhere on the board
/ATmega4808 and Peripherals/Signal_Relay: U10.25 (PA3); also elsewhere on the board
GND: C13.2, C14.2, C15.1, C16.2, C17.1, C21.2, C22.2, D2.1, D3.1, D4.1, D7.1, J3.1, J4.1, J5.2, Q1.2 (S), R7.2, R11.2, R39.1, U7.5 (GND), U8.3 (GND), U9.1 (GND), U9.15 (GND), U9.38 (GND), U9.39 (GND), U10.15 (GND), U10.21 (GND); also elsewhere on the board
unnamed: D7.3, R24.2, R39.2, U10.10 (PD4)
unnamed: Q1.1 (G), R7.1, U10.9 (PD3)
unnamed: R8.1, U10.28 (PA6)
unnamed: R9.1, U10.27 (PA5)
unnamed: R10.1, U10.26 (PA4)

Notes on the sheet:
RS485 Driver
ATmega/ESP Serial Link (incl. Programming Atmega via J4)
ATmega Extension Connector
Lock Driver
ATmega/ESP Programming Header (Custom Pinout)
Operator Controls

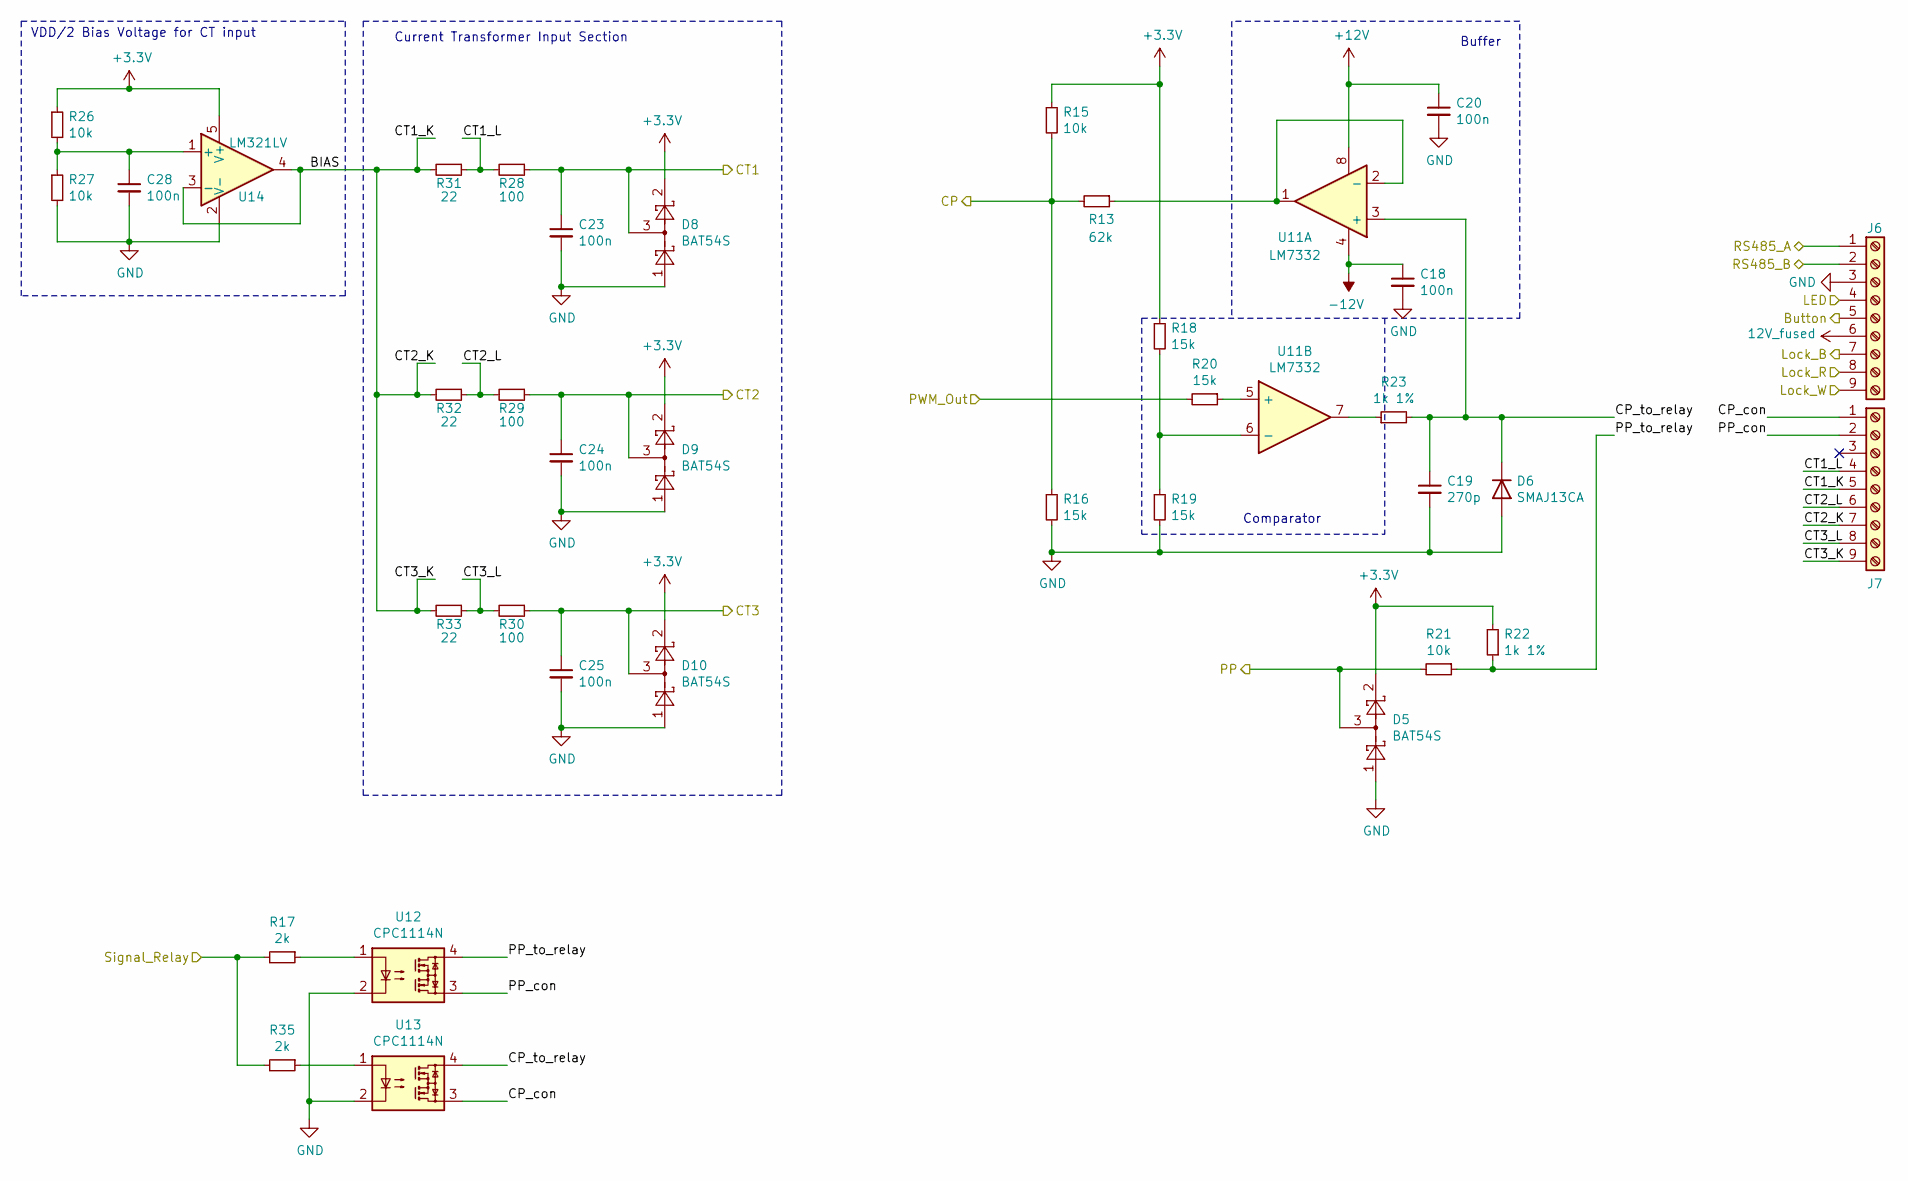
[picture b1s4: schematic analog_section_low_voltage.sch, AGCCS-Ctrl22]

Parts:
C18, C20, C23, C24, C25, C28: 100n; C_0805_2012Metric_Pad1.18x1.45mm_HandSolder; PartNo 963-EMF212B7104KGHT
C19: 270p; C_0805_2012Metric_Pad1.15x1.40mm_HandSolder; PartNo 77-VJ0805A271KXJPBC
D5, D8, D9, D10: BAT54S; SOT-23_Handsoldering; PartNo 757-TBAT54SLM
D6: SMAJ13CA; D_SMA_Handsoldering; PartNo 652-SMAJ13CA
J6: Screw_Terminal_01x09; lv_screw_9pin_1; PartNo na
J7: Screw_Terminal_01x09; lv_screw_9pin_2; PartNo 490-TB004-508-18BE
R13: 62k; R_0603_1608Metric_Pad1.05x0.95mm_HandSolder; PartNo 594-MCT06030C6202FP5
R15, R21, R26, R27: 10k; R_0603_1608Metric_Pad1.05x0.95mm_HandSolder; PartNo 594-MCT06030C1002FP5
R16, R18, R19, R20: 15k; R_0603_1608Metric_Pad1.05x0.95mm_HandSolder; PartNo 594-MCT06030C1502FP5
R17, R35: 2k; R_0603_1608Metric_Pad1.05x0.95mm_HandSolder; PartNo 594-MCT06030C2001FP5
R22, R23: 1k 1%; R_0603_1608Metric_Pad1.05x0.95mm_HandSolder; PartNo 594-MCT06030C1001FP5
R28, R29, R30: 100; R_0603_1608Metric_Pad1.05x0.95mm_HandSolder; PartNo 490-TB005-762-10BE
R31, R32, R33: 22; R_0603_1608Metric_Pad1.05x0.95mm_HandSolder; PartNo 594-MCT06030C2209FP5
U11: LM7332; SOIC-8_3.9x4.9mm_P1.27mm; PartNo 926-LM7332MA/NOPB
U12, U13: CPC1114N; SOP-4_3.8x4.1mm_P2.54mm; PartNo 849-CPC1114N
U14: LM321LV; SOT-23-5; PartNo 595-LM321LVIDBVR

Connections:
12V_fused: J6.6; also elsewhere on the board
+3V3: D5.2, D8.2, D9.2, D10.2, R15.1, R18.1, R22.2, R26.1, U14.5 (V+); also elsewhere on the board
+12V: C20.1, U11.8 (V+); also elsewhere on the board
-12V: C18.1, U11.4 (V-); also elsewhere on the board
/ATmega4808 and Peripherals/Button: J6.5; also elsewhere on the board
/ATmega4808 and Peripherals/CP: R13.2, R15.2, R16.1; also elsewhere on the board
/ATmega4808 and Peripherals/CT1: C23.1, D8.3, R28.1; also elsewhere on the board
/ATmega4808 and Peripherals/CT2: C24.1, D9.3, R29.1; also elsewhere on the board
/ATmega4808 and Peripherals/CT3: C25.1, D10.3, R30.1; also elsewhere on the board
/ATmega4808 and Peripherals/LED: J6.4; also elsewhere on the board
/ATmega4808 and Peripherals/Lock_B: J6.7; also elsewhere on the board
/ATmega4808 and Peripherals/Lock_R: J6.8; also elsewhere on the board
/ATmega4808 and Peripherals/Lock_W: J6.9; also elsewhere on the board
/ATmega4808 and Peripherals/PP: D5.3, R21.2; also elsewhere on the board
/ATmega4808 and Peripherals/PWM_Out: R20.2; also elsewhere on the board
/ATmega4808 and Peripherals/RS485_A: J6.1; also elsewhere on the board
/ATmega4808 and Peripherals/RS485_B: J6.2; also elsewhere on the board
/ATmega4808 and Peripherals/Signal_Relay: R17.2, R35.2; also elsewhere on the board
/Analog Section and Low Voltage Outputs/BIAS: J7.5, J7.7, J7.9, R31.2, R32.2, R33.2, U14.3 (-), U14.4
/Analog Section and Low Voltage Outputs/CP_con: J7.1, U13.3
/Analog Section and Low Voltage Outputs/CP_to_relay: C19.1, D6.1 (K), R23.2, U11.3 (+), U13.4
/Analog Section and Low Voltage Outputs/CT1_L: J7.4, R28.2, R31.1
/Analog Section and Low Voltage Outputs/CT2_L: J7.6, R29.2, R32.1
/Analog Section and Low Voltage Outputs/CT3_L: J7.8, R30.2, R33.1
/Analog Section and Low Voltage Outputs/PP_con: J7.2, U12.3
/Analog Section and Low Voltage Outputs/PP_to_relay: R21.1, R22.1, U12.4
GND: C18.2, C19.2, C20.2, C23.2, C24.2, C25.2, C28.2, D5.1, D6.2 (A), D8.1, D9.1, D10.1, J6.3, R16.2, R19.2, R27.2, U12.2, U13.2, U14.2 (V-); also elsewhere on the board
unnamed: C28.1, R26.2, R27.1, U14.1 (+)
unnamed: R13.1, U11.1, U11.2 (-)
unnamed: R17.1, U12.1
unnamed: R18.2, R19.1, U11.6 (-)
unnamed: R20.1, U11.5 (+)
unnamed: R23.1, U11.7
unnamed: R35.1, U13.1

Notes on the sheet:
Buffer
Comparator
Current Transformer Input Section
VDD/2 Bias Voltage for CT input

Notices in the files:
ctrl22/ctrl22.c:
Copyright Thomas Moor 2020-2021
Copyright Thomas Moor (c) 2020, 2021");
